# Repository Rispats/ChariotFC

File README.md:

# ChariotFC

> Custom Flight Controller + PDB for General Free Style and Auotpilot applications

## Specs
- **FMU:** AT32F435RMT7 (288Mhz, Hardware FPU)
- **Power Distrubution Board:** 2S-6S LiPo 
- **From Factor:** 30.5mm X 30.5mm Dual stack (FC + PDB)
- **Target Firmware:** PX4, Betaflight

STATUS: PCB Design in progress

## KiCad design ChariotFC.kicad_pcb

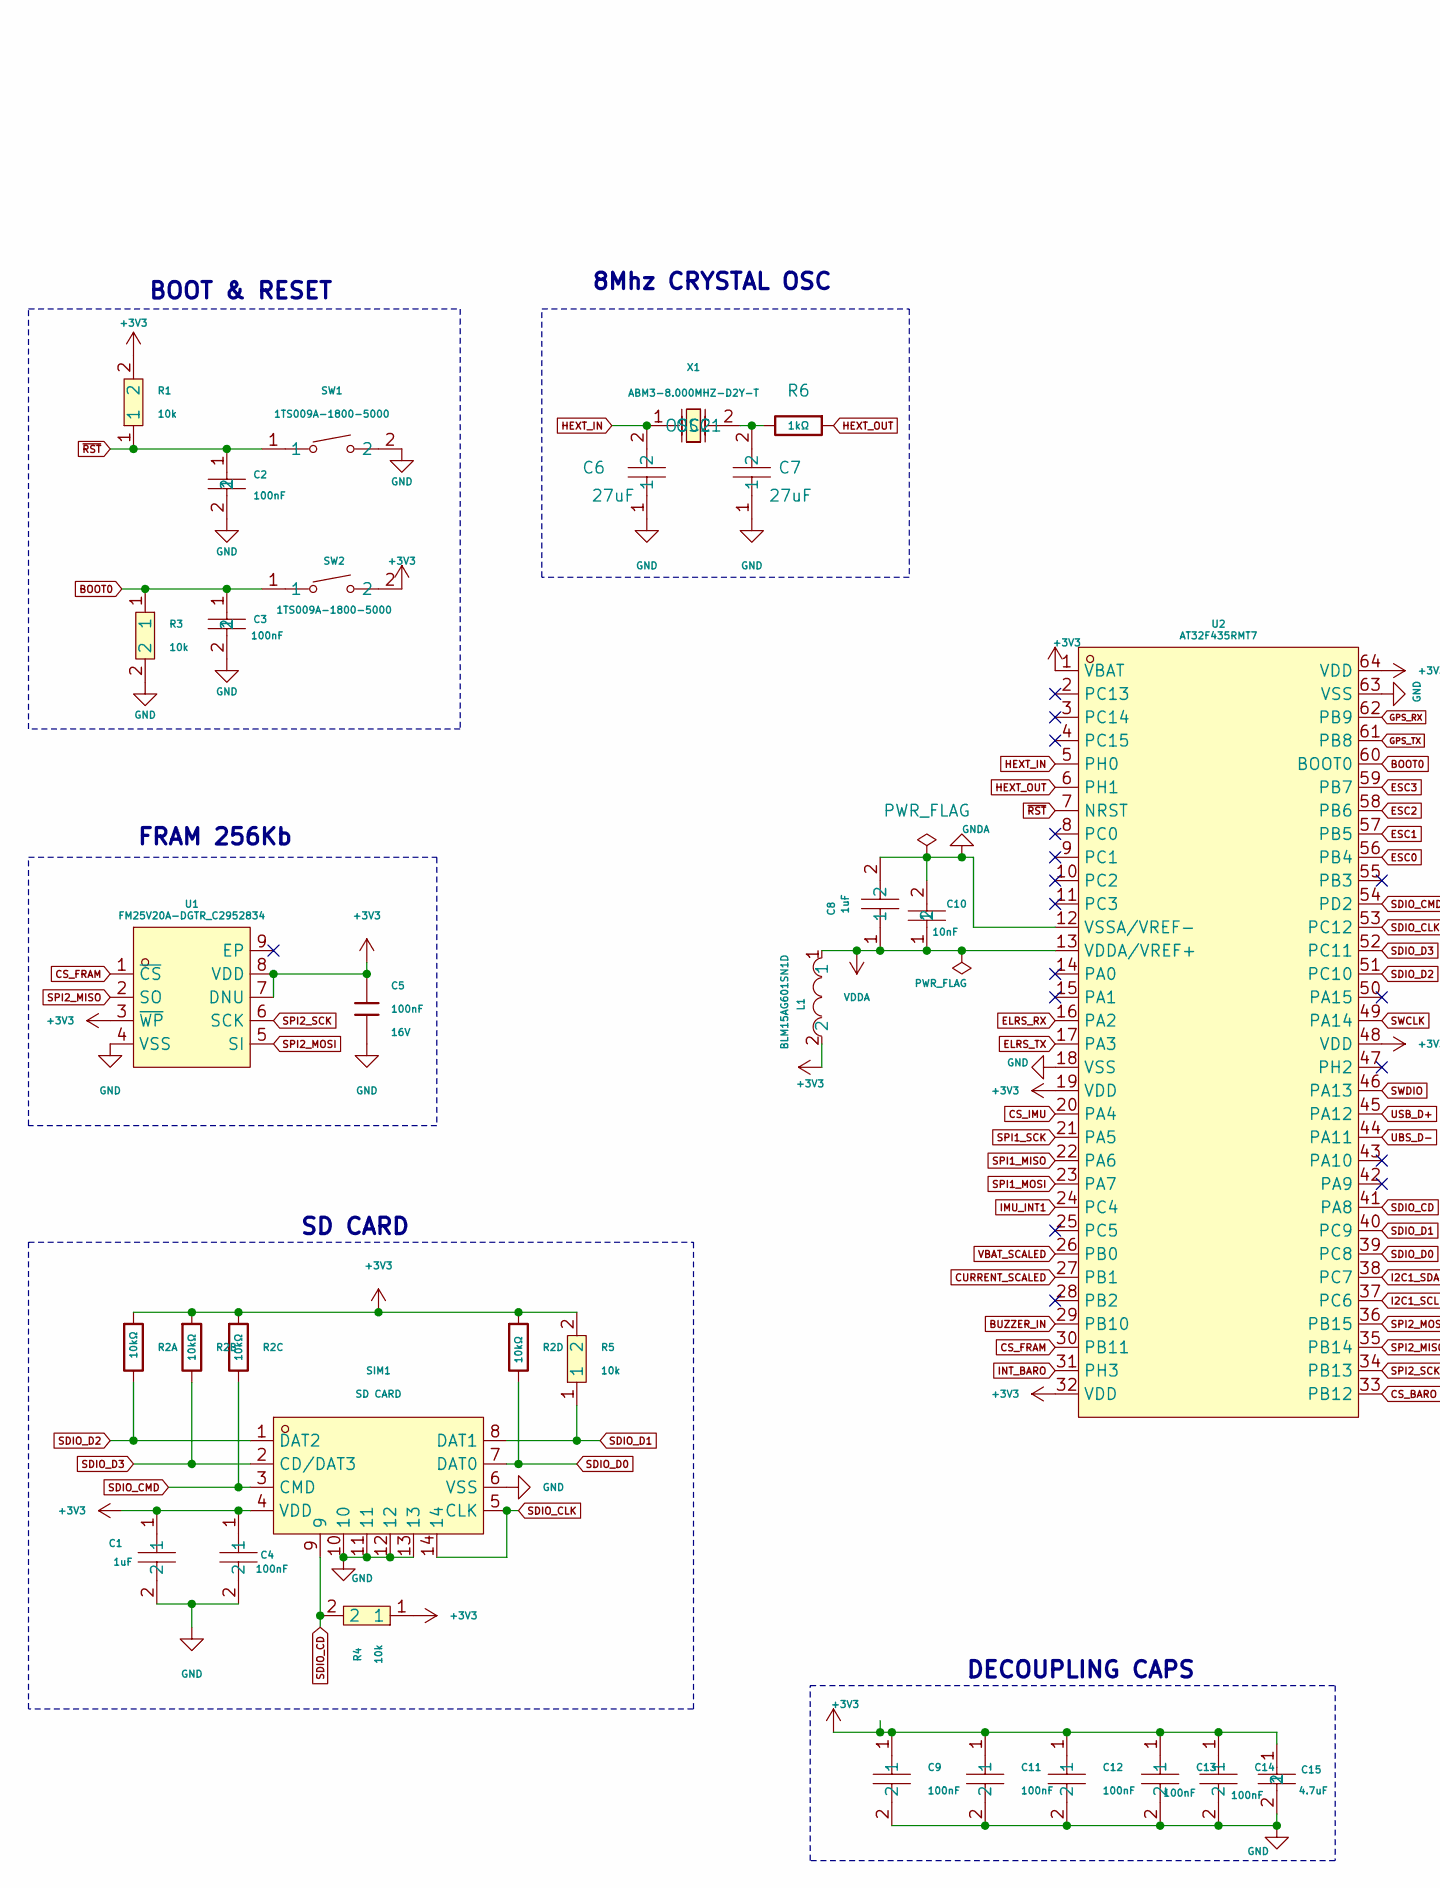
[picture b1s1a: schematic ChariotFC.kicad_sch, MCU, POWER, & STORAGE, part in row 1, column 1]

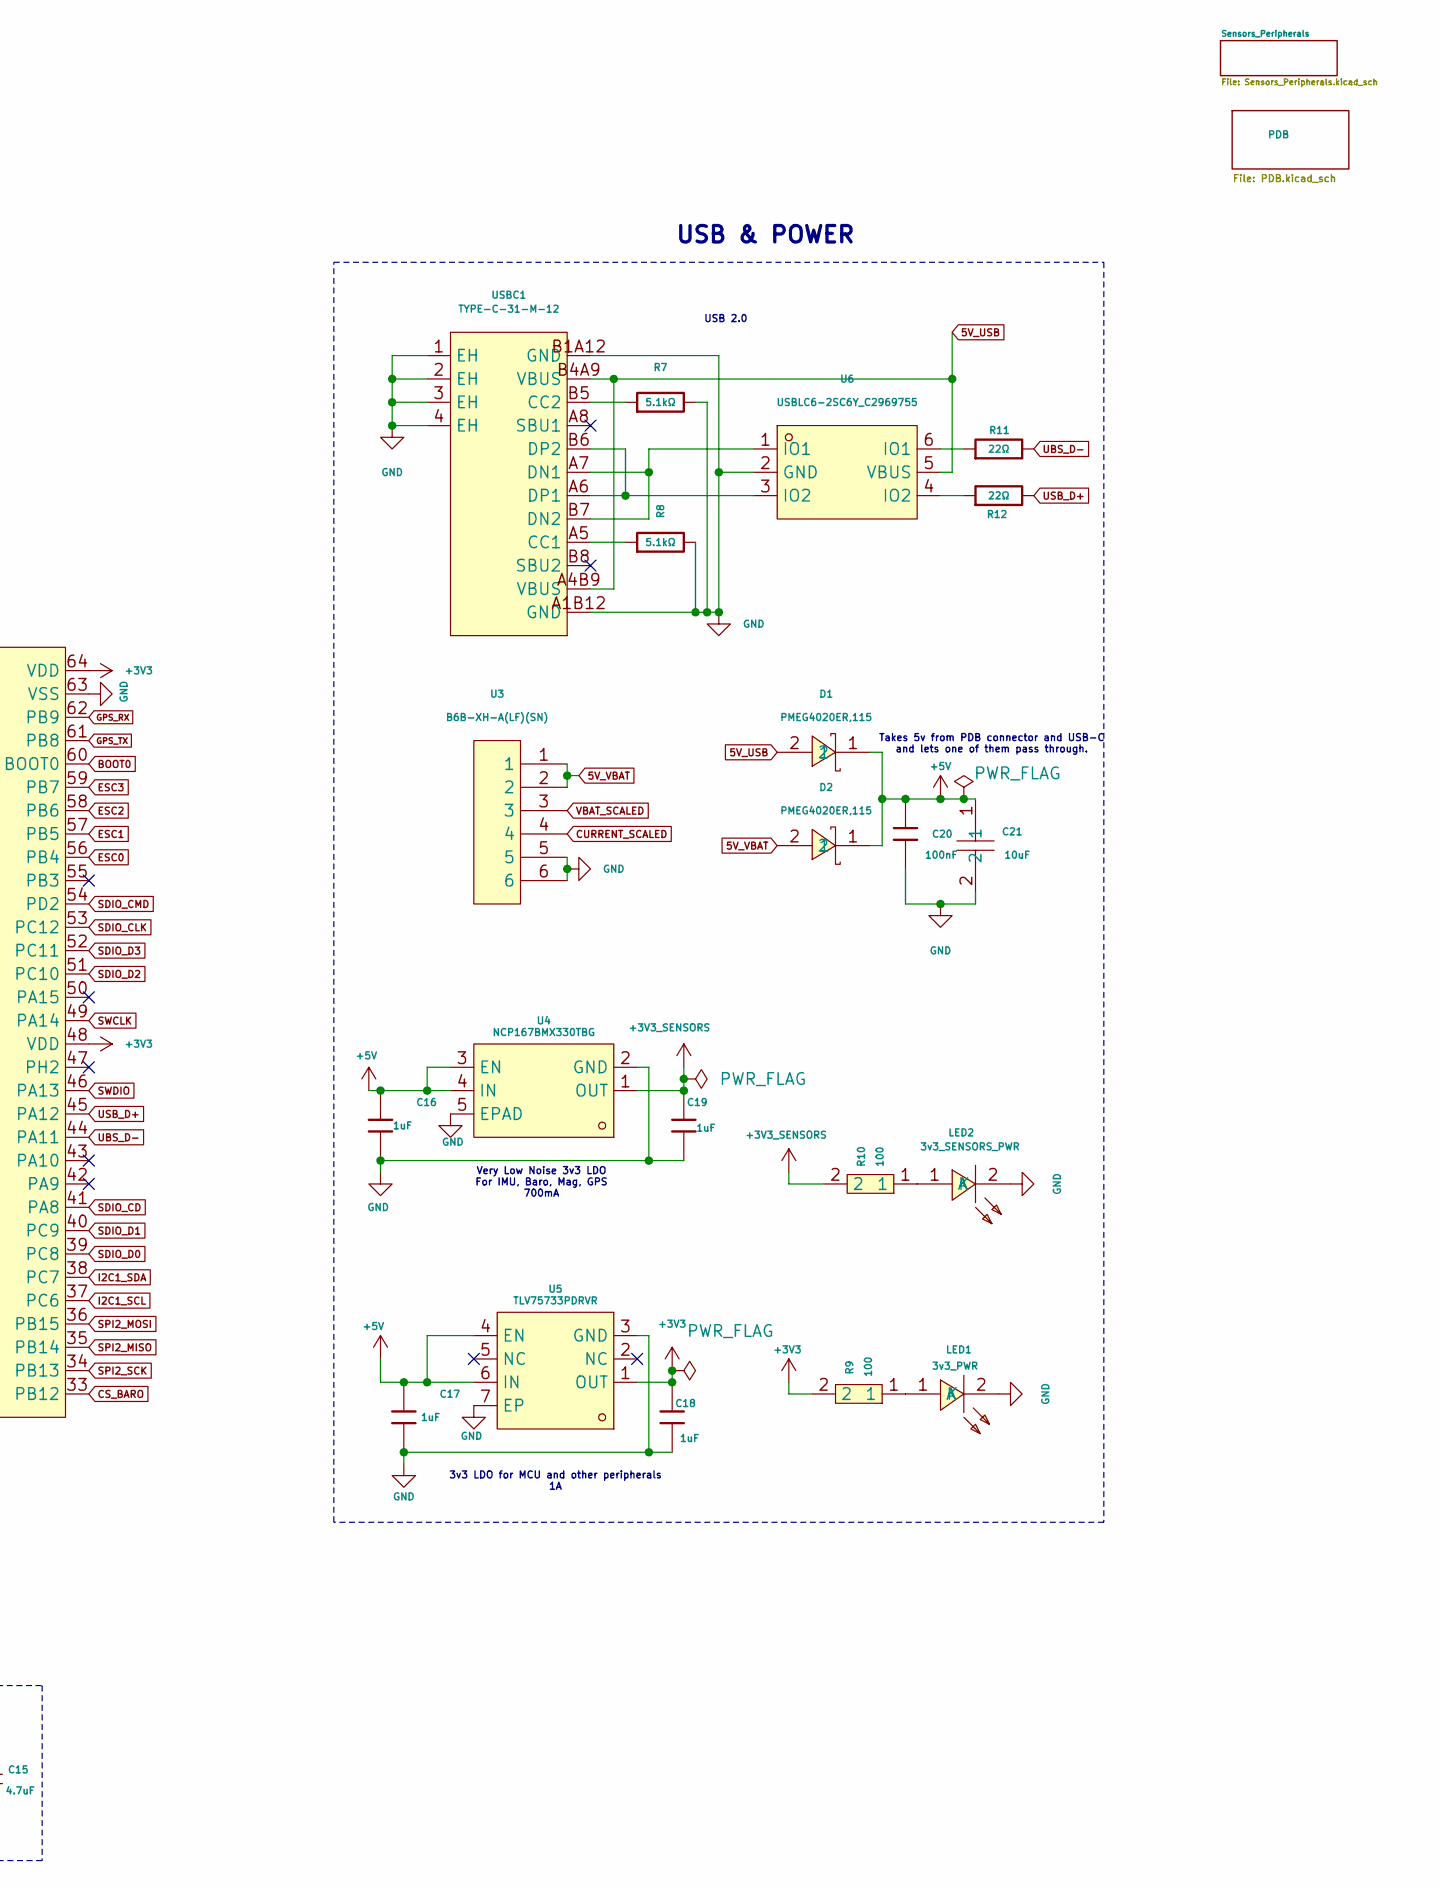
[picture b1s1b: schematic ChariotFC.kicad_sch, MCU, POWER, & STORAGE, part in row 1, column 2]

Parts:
C1: 1uF; C0402; LCSC Part C52923
C2, C3: 100nF; C0402; LCSC Part C77019
C4, C9, C11, C12, C13, C14: 100nF; C0402; LCSC Part C1525
C5, C20: 100nF; C0402; Voltage Rated 16V; Tolerance ±10%; Part CL05B104KO5NNNC; LCSC C1525
C6, C7: 27uF; C0402; LCSC Part C445761
C8: 1uF; C0402; LCSC Part C15684
C10: 10nF; C0402; LCSC Part C77019
C15: 4.7uF; C0805; LCSC Part C1779
C16, C17, C18, C19: 1uF; C0402; Voltage Rated 25V; Tolerance ±10%; Part CL05A105KA5NQNC; LCSC C52923
C21: 10uF; C1206; LCSC Part C6119987
D1, D2: PMEG4020ER,115; SOD-123_L2.8-W1.8-LS3.7-RD; LCSC Part C255588
L1: BLM15AG601SN1D; L0402; LCSC Part C76884
LED1: 3v3_PWR; LED0805-R-RD; LCSC Part C2297
LED2: 3v3_SENSORS_PWR; LED0805-R-RD; LCSC Part C2297
R1, R3, R4, R5: 10k; R0402; LCSC Part C60490
R2: 10kΩ; RES-ARRAY-SMD_0402-8P-L2.0-W1.0-BL; Tolerance ±5%; Part 4D02WGJ0103TCE; LCSC C25725
R6: 1kΩ; R0402; Overload Voltage (Max) 50V; Tolerance ±1%; Part 0402WGF1001TCE; LCSC C11702
R7, R8: 5.1kΩ; R0402; Overload Voltage (Max) 50V; Tolerance ±1%; Part 0402WGF5101TCE; LCSC C25905
R9, R10: 100; R0402; LCSC Part C25076
R11, R12: 22Ω; R0402; Overload Voltage (Max) 50V; Tolerance ±1%; Part 0402WGF220JTCE; LCSC C25092
SIM1: SD CARD; SIM-SMD_8P-1040310811; LCSC Part C585350
SW1, SW2: 1TS009A-1800-5000; KEY-SMD_L6.0-W6.0-LS6.6; LCSC Part C319409
U1: FM25V20A-DGTR_C2952834; DFN-8_L6.0-W5.0-P1.27-BL-EP; LCSC Part C2952834
U2: AT32F435RMT7; LQFP-64_L10.0-W10.0-P0.50-LS12.0-BL; LCSC Part C5178940
U3: B6B-XH-A(LF)(SN); CONN-TH_6P-P2.50_B6B-XH-A-LF-SN; LCSC Part C144397
U4: NCP167BMX330TBG; XDFN-4_L1.0-W1.0-P0.65-BL-EP; LCSC Part C892227
U5: TLV75733PDRVR; TDFN-6_L2.0-W2.0-P0.65-TL-EP; LCSC Part C2868428
U6: USBLC6-2SC6Y_C2969755; SOT-23-6_L2.9-W1.7-P0.95-LS2.8-BL; LCSC Part C2969755
USBC1: TYPE-C-31-M-12; USB-C_SMD-TYPE-C-31-M-12_1; LCSC Part C165948
X1: ABM3-8.000MHZ-D2Y-T; OSC-SMD_L5.0-W3.2; LCSC Part C144380

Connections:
5V_USB: D1.2, U6.5 (VBUS), USBC1.A4B9 (VBUS), USBC1.B4A9 (VBUS)
5V_VBAT: D2.2, U3.1, U3.2; also elsewhere on the board
+3V3: C1.1, C4.1, C5.1, C9.1, C11.1, C12.1, C13.1, C14.1, C15.1, C18.1, L1.2, R1.2, R2.1, R2.2, R2.3, R2.4, R4.1, R5.2, R9.2, SIM1.4 (VDD), SW2.2, U1.3 (~WP), U1.7 (DNU), U1.8 (VDD), U2.1 (VBAT), U2.19 (VDD), U2.32 (VDD), U2.48 (VDD), U2.64 (VDD), U5.1 (OUT); also elsewhere on the board
+3V3_SENSORS: C19.1, R10.2, U4.1 (OUT); also elsewhere on the board
+5V: C16.1, C17.1, C20.2, C21.1, D1.1, D2.1, U4.3 (EN), U4.4 (IN), U5.4 (EN), U5.6 (IN); also elsewhere on the board
BOOT0: C3.1, R3.1, SW2.1, U2.60 (BOOT0)
BUZZER_IN: U2.29 (PB10); also elsewhere on the board
CS_BARO: U2.33 (PB12); also elsewhere on the board
CS_FRAM: U1.1 (~CS), U2.30 (PB11)
CS_IMU: U2.20 (PA4); also elsewhere on the board
CURRENT_SCALED: U2.27 (PB1), U3.4; also elsewhere on the board
ELRS_RX: U2.16 (PA2); also elsewhere on the board
ELRS_TX: U2.17 (PA3); also elsewhere on the board
ESC0: U2.56 (PB4); also elsewhere on the board
ESC1: U2.57 (PB5); also elsewhere on the board
ESC2: U2.58 (PB6); also elsewhere on the board
ESC3: U2.59 (PB7); also elsewhere on the board
GND: C1.2, C2.2, C3.2, C4.2, C5.2, C6.1, C7.1, C9.2, C11.2, C12.2, C13.2, C14.2, C15.2, C16.2, C17.2, C18.2, C19.2, C20.1, C21.2, LED1.2 (K), LED2.2 (K), R3.2, R7.2, R8.2, SIM1.6 (VSS), SIM1.10, SIM1.11, SIM1.12, SIM1.13, SW1.2, U1.4 (VSS), U2.18 (VSS), U2.63 (VSS), U3.5, U3.6, U4.2 (GND), U4.5 (EPAD), U5.3 (GND), U5.7 (EP), U6.2 (GND), USBC1.1 (EH), USBC1.2 (EH), USBC1.3 (EH), USBC1.4 (EH), USBC1.A1B12 (GND), USBC1.B1A12 (GND); also elsewhere on the board
GNDA: C8.2, C10.2, U2.12 (VSSA/VREF-)
GPS_RX: U2.62 (PB9); also elsewhere on the board
GPS_TX: U2.61 (PB8); also elsewhere on the board
HEXT_IN: C6.2, U2.5 (PH0), X1.1 (OSC1); also elsewhere on the board
HEXT_OUT: R6.1, U2.6 (PH1)
I2C1_SCL: U2.37 (PC6); also elsewhere on the board
I2C1_SDA: U2.38 (PC7); also elsewhere on the board
IMU_INT1: U2.24 (PC4); also elsewhere on the board
INT_BARO: U2.31 (PH3); also elsewhere on the board
unnamed: LED1.1 (A), R9.1
unnamed: LED2.1 (A), R10.1
unnamed: R11.1, U6.6 (IO1)
unnamed: R12.1, U6.4 (IO2)
unnamed: R8.1, USBC1.A5 (CC1)
unnamed: R7.1, USBC1.B5 (CC2)
unnamed: U6.1 (IO1), USBC1.A7 (DN1), USBC1.B7 (DN2)
unnamed: U6.3 (IO2), USBC1.A6 (DP1), USBC1.B6 (DP2)
unnamed 56: C7.2, R6.2, X1.2 (OSC2); also elsewhere on the board
SDIO_CD: R4.2, SIM1.9, U2.41 (PA8)
SDIO_CLK: SIM1.5 (CLK), SIM1.14, U2.53 (PC12)
SDIO_CMD: R2.6, SIM1.3 (CMD), U2.54 (PD2)
SDIO_D0: R2.5, SIM1.7 (DAT0), U2.39 (PC8)
SDIO_D1: R5.1, SIM1.8 (DAT1), U2.40 (PC9)
SDIO_D2: R2.8, SIM1.1 (DAT2), U2.51 (PC10)
SDIO_D3: R2.7, SIM1.2 (CD/DAT3), U2.52 (PC11)
SPI1_MISO: U2.22 (PA6); also elsewhere on the board
SPI1_MOSI: U2.23 (PA7); also elsewhere on the board
SPI1_SCK: U2.21 (PA5); also elsewhere on the board
SPI2_MISO: U1.2 (SO), U2.35 (PB14); also elsewhere on the board
SPI2_MOSI: U1.5 (SI), U2.36 (PB15); also elsewhere on the board
SPI2_SCK: U1.6 (SCK), U2.34 (PB13); also elsewhere on the board
SWCLK: U2.49 (PA14); also elsewhere on the board
SWDIO: U2.46 (PA13); also elsewhere on the board
UBS_D-: R11.2, U2.44 (PA11)
USB_D+: R12.2, U2.45 (PA12)
VBAT_SCALED: U2.26 (PB0), U3.3; also elsewhere on the board
VDDA: C8.1, C10.1, L1.1, U2.13 (VDDA/VREF+)
~RST: C2.1, R1.1, SW1.1, U2.7 (NRST)

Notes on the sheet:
3v3 LDO for MCU and other peripherals 1A
USB & POWER
USB 2.0
Takes 5v from PDB connector and USB-C and lets one of them pass through.
SD CARD
DECOUPLING CAPS
BOOT & RESET
FRAM 256Kb
8Mhz CRYSTAL OSC
Very Low Noise 3v3 LDO For IMU, Baro, Mag, GPS 700mA

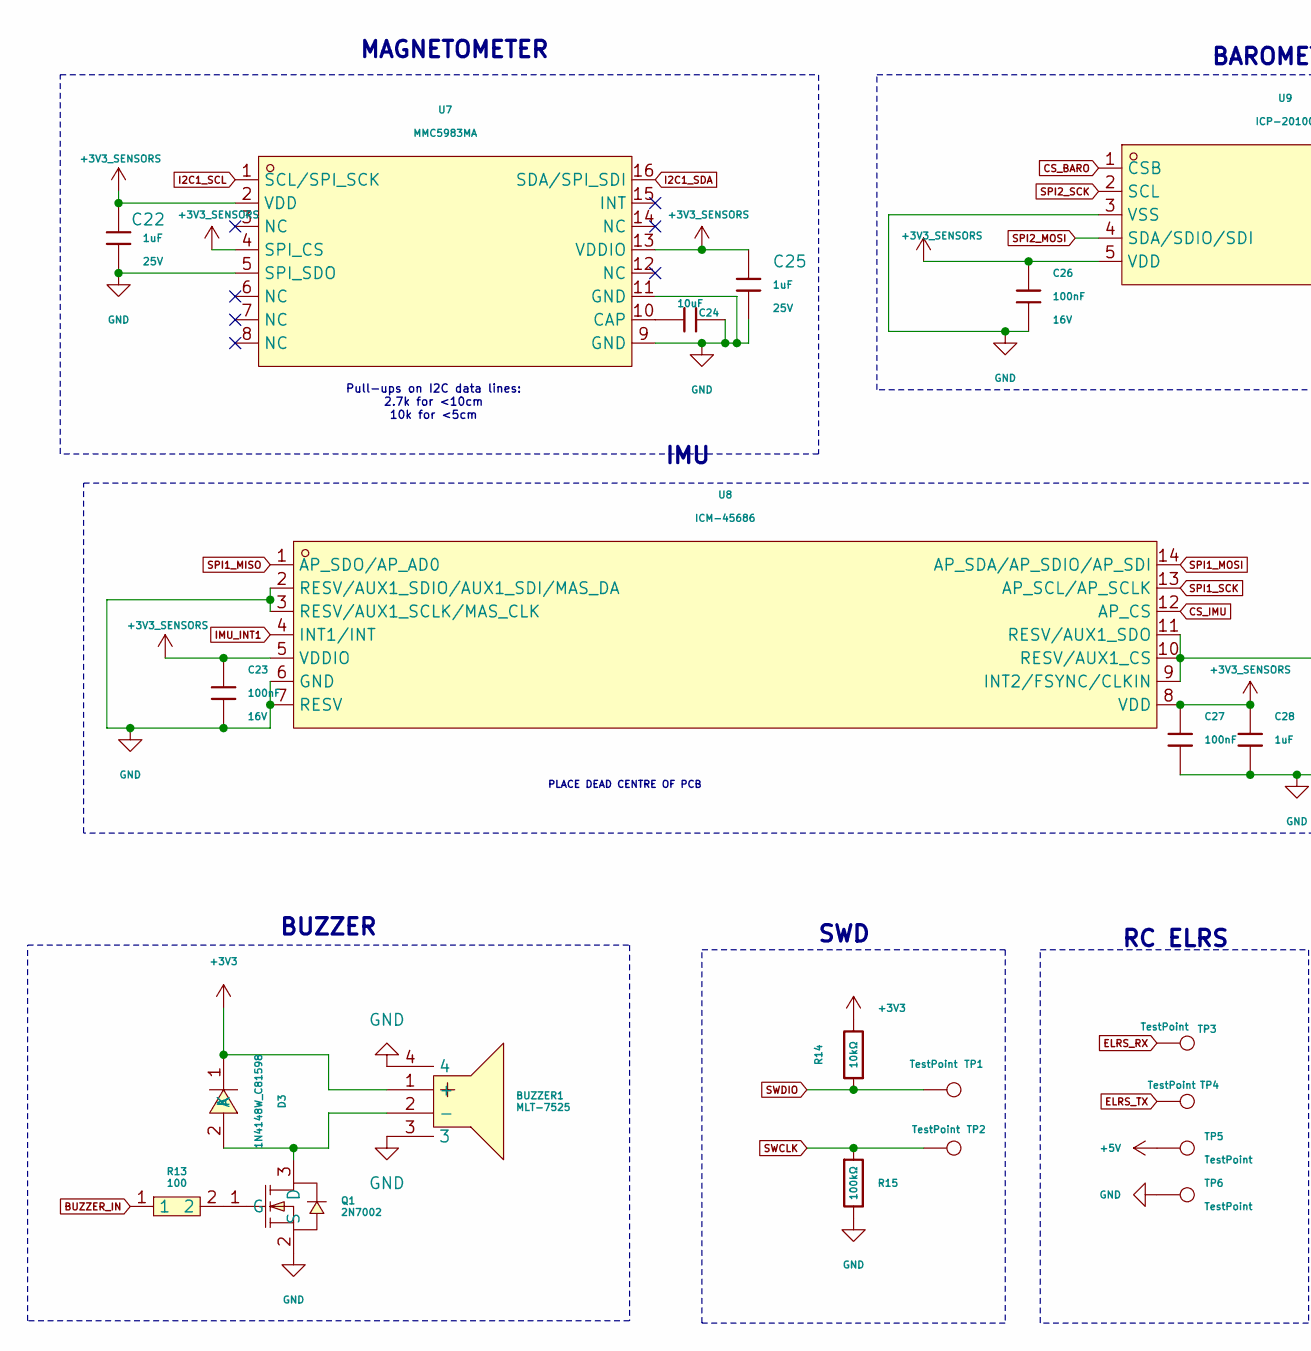
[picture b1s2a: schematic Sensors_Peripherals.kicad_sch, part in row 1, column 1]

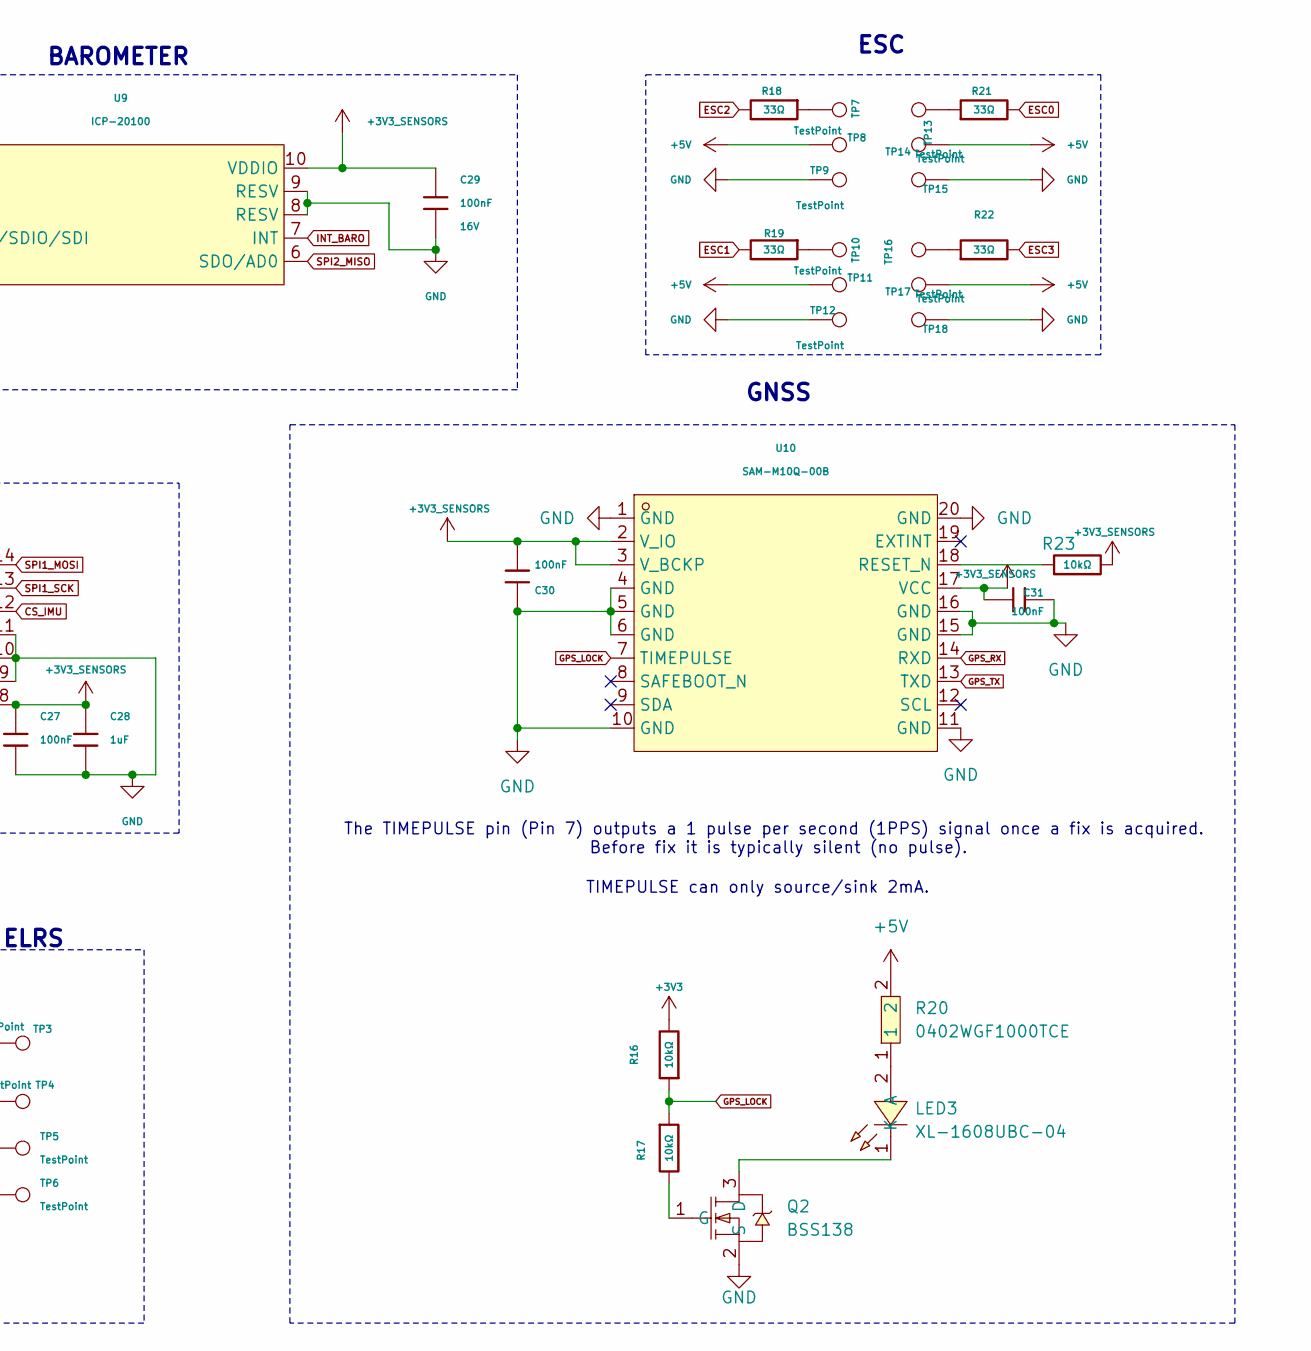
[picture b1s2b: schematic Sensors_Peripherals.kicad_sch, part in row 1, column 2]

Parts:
BUZZER1: MLT-7525; BUZ-SMD_4P-L7.5-W7.5-P7.59-TL; LCSC Part C95299
C22, C25, C28: 1uF; C0402; Voltage Rated 25V; Tolerance ±10%; Part CL05A105KA5NQNC; LCSC C52923
C23, C26, C27, C29, C30, C31: 100nF; C0402; Voltage Rated 16V; Tolerance ±10%; Part CL05B104KO5NNNC; LCSC C1525
C24: 10uF; C0603; Voltage Rated 10V; Tolerance ±10%; Part CL10A106KP8NNNC; LCSC C19702
D3: 1N4148W_C81598; SOD-123F_L2.7-W1.6-LS3.8-RD; LCSC Part C81598
LED3: XL-1608UBC-04; LED0603-RD_BLUE; MPN XL-1608UBC-04; LCSC Part C965807
Q1: 2N7002; SOT-23-3_L2.9-W1.3-P1.90-LS2.4-BR; LCSC Part C8545
Q2: BSS138; SOT-23-3_L2.9-W1.6-P1.90-LS2.8-BR; MPN BSS138; LCSC Part C52895
R13: 100; R0402; LCSC Part C25076
R14, R16, R17: 10kΩ; R0402; Overload Voltage (Max) 50V; Tolerance ±1%; Part 0402WGF1002TCE; LCSC C25744
R15: 100kΩ; R0402; Overload Voltage (Max) 50V; Tolerance ±1%; Part 0402WGF1003TCE; LCSC C25741
R18, R19: 33Ω; R0402; Overload Voltage (Max) 50V; Tolerance ±1%; Part 0402WGF330JTCE; LCSC C25105
R20: 0402WGF1000TCE; R0402; MPN 0402WGF1000TCE; LCSC Part C25076
R21, R22: 33Ω; C0402; Overload Voltage (Max) 50V; Tolerance ±1%; Part 0402WGF330JTCE; LCSC C25105
R23: 10kΩ; C0402; Overload Voltage (Max) 50V; Tolerance ±1%; Part 0402WGF1002TCE; LCSC C25744
TP1, TP2: TestPoint; TestPoint_THTPad_D2.0mm_Drill1.0mm
TP3, TP4, TP5, TP6, TP7, TP8, TP9, TP10, TP11, TP12, TP13, TP14, TP15, TP16, TP17, TP18: TestPoint; TestPoint_Pad_4.0x4.0mm
U7: MMC5983MA; LGA-16_L3.0-W3.0-P0.50-BL_SQ; LCSC Part C404329
U8: ICM-45686; LGA-14_L3.0-W2.5-P0.50-TL; LCSC Part C22459454
U9: ICP-20100; LGA-10_L2.0-W2.0-P0.50-TL_ICP-20100; LCSC Part C5343527
U10: SAM-M10Q-00B; LCC-20_L15.5-W15.5-P1.90_SAM-M10Q-00B; LCSC Part C5443880

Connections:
+3V3: BUZZER1.1 (+), D3.1 (K), R14.2, R16.2; also elsewhere on the board
+3V3_SENSORS: C22.1, C23.1, C25.1, C26.2, C27.1, C28.1, C29.1, C30.1, C31.1, R23.2, U7.2 (VDD), U7.4 (SPI_CS), U7.13 (VDDIO), U8.5 (VDDIO), U8.8 (VDD), U9.5 (VDD), U9.10 (VDDIO), U10.2 (V_IO), U10.3 (V_BCKP), U10.17 (VCC); also elsewhere on the board
+5V: R20.2, TP5.1 (1_1), TP8.1 (1_1), TP11.1 (1_1), TP14.1 (1_1), TP17.1 (1_1); also elsewhere on the board
BUZZER_IN: R13.1; also elsewhere on the board
CS_BARO: U9.1 (CSB); also elsewhere on the board
CS_IMU: U8.12 (AP_CS); also elsewhere on the board
ELRS_RX: TP3.1 (1_1); also elsewhere on the board
ELRS_TX: TP4.1 (1_1); also elsewhere on the board
ESC0: R21.2; also elsewhere on the board
ESC1: R19.2; also elsewhere on the board
ESC2: R18.2; also elsewhere on the board
ESC3: R22.2; also elsewhere on the board
GND: BUZZER1.3, BUZZER1.4, C22.2, C23.2, C24.2, C25.2, C26.1, C27.2, C28.2, C29.2, C30.2, C31.2, Q1.2 (S), Q2.2 (S), R15.2, TP6.1 (1_1), TP9.1 (1_1), TP12.1 (1_1), TP15.1 (1_1), TP18.1 (1_1), U7.5 (SPI_SDO), U7.9 (GND), U7.11 (GND), U8.2 (RESV/AUX1_SDIO/AUX1_SDI/MAS_DA), U8.3 (RESV/AUX1_SCLK/MAS_CLK), U8.6 (GND), U8.7 (RESV), U8.9 (INT2/FSYNC/CLKIN), U8.10 (RESV/AUX1_CS), U8.11 (RESV/AUX1_SDO), U9.3 (VSS), U9.8 (RESV), U9.9 (RESV), U10.1 (GND), U10.4 (GND), U10.5 (GND), U10.6 (GND), U10.10 (GND), U10.11 (GND), U10.15 (GND), U10.16 (GND), U10.20 (GND); also elsewhere on the board
GPS_LOCK: R16.1, R17.1, U10.7 (TIMEPULSE)
GPS_RX: U10.14 (RXD); also elsewhere on the board
GPS_TX: U10.13 (TXD); also elsewhere on the board
I2C1_SCL: U7.1 (SCL/SPI_SCK); also elsewhere on the board
I2C1_SDA: U7.16 (SDA/SPI_SDI); also elsewhere on the board
IMU_INT1: U8.4 (INT1/INT); also elsewhere on the board
INT_BARO: U9.7 (INT); also elsewhere on the board
unnamed: BUZZER1.2 (-), D3.2 (A), Q1.3 (D)
unnamed: LED3.2 (A), R20.1
unnamed: LED3.1 (K), Q2.3 (D)
unnamed: Q1.1 (G), R13.2
unnamed: Q2.1 (G), R17.2
unnamed: R18.1, TP7.1 (1_1)
unnamed: R19.1, TP10.1 (1_1)
unnamed: R21.1, TP13.1 (1_1)
unnamed: R22.1, TP16.1 (1_1)
unnamed: C24.1, U7.10 (CAP)
unnamed: R23.1, U10.18 (RESET_N)
SPI1_MISO: U8.1 (AP_SDO/AP_AD0); also elsewhere on the board
SPI1_MOSI: U8.14 (AP_SDA/AP_SDIO/AP_SDI); also elsewhere on the board
SPI1_SCK: U8.13 (AP_SCL/AP_SCLK); also elsewhere on the board
SPI2_MISO: U9.6 (SDO/AD0); also elsewhere on the board
SPI2_MOSI: U9.4 (SDA/SDIO/SDI); also elsewhere on the board
SPI2_SCK: U9.2 (SCL); also elsewhere on the board
SWCLK: R15.1, TP2.1 (1_1); also elsewhere on the board
SWDIO: R14.1, TP1.1 (1_1); also elsewhere on the board

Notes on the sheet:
BAROMETER
ESC
SWD
The TIMEPULSE pin (Pin 7) outputs a 1 pulse per second (1PPS) signal once a fix is acquired. Before fix it is typically silent (no pulse).
IMU
PLACE DEAD CENTRE OF PCB
TIMEPULSE can only source/sink 2mA.
MAGNETOMETER
RC ELRS
GNSS
BUZZER
Pull-ups on I2C data lines: 2.7k for <10cm 10k for <5cm

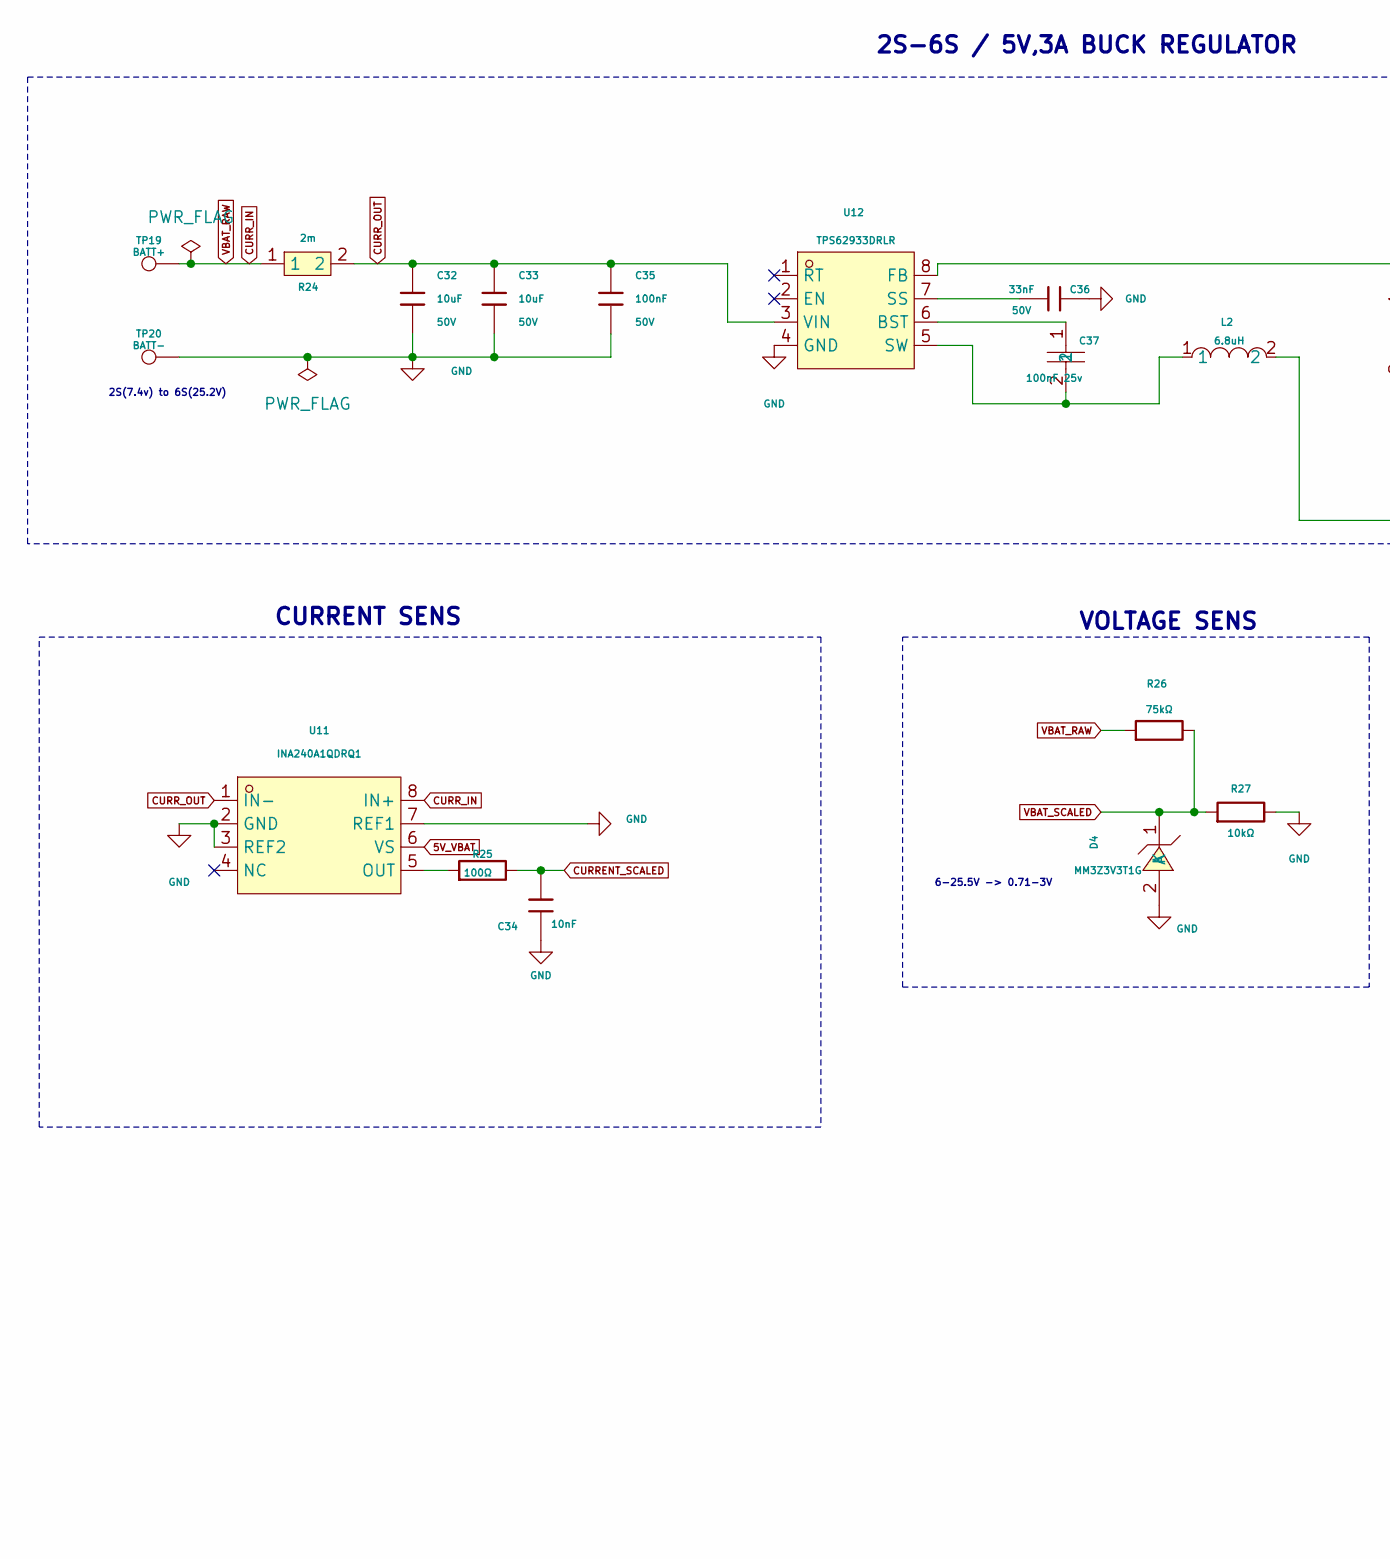
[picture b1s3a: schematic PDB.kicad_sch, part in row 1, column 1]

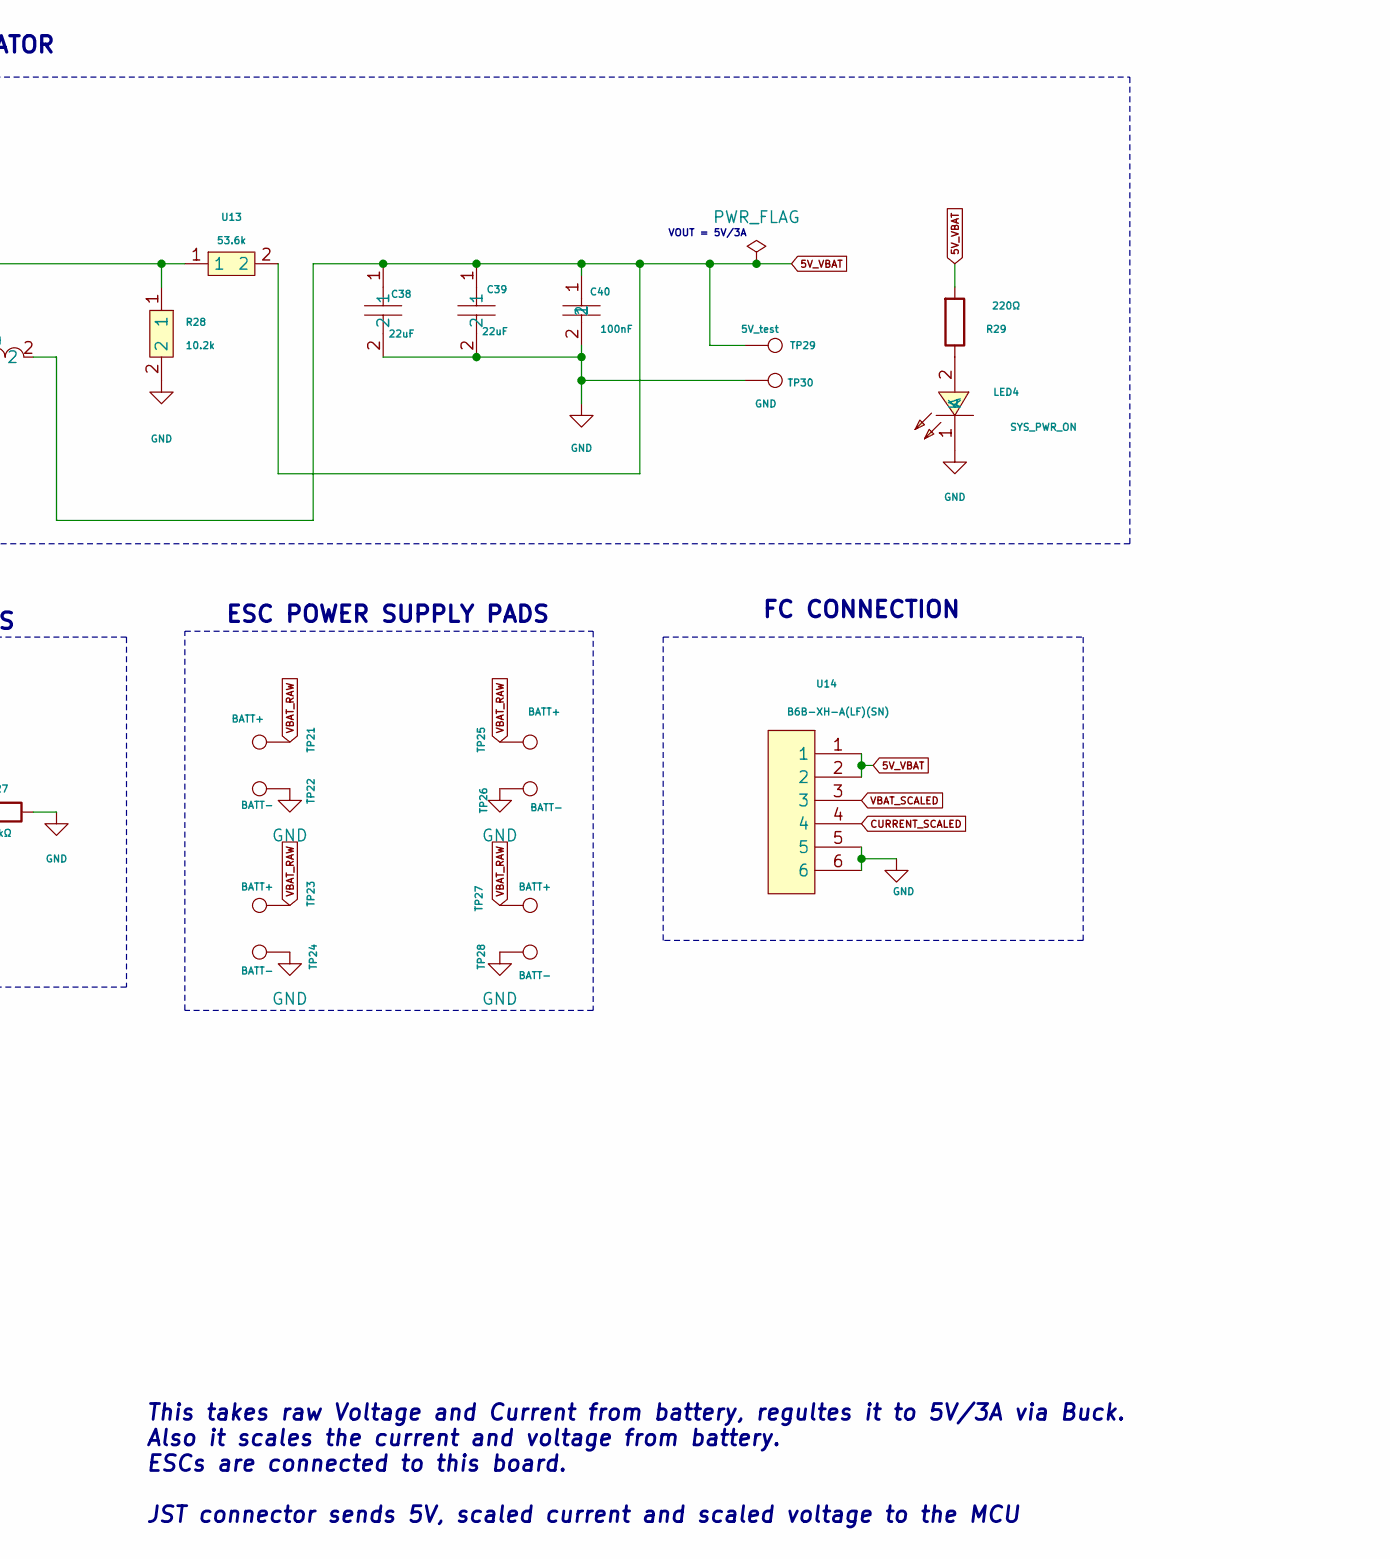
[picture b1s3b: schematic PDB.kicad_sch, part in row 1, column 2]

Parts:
C32, C33: 10uF; C0805; Voltage Rated 50V; Tolerance ±10%; Part GRM21BR61H106KE43L; LCSC C440198
C34: 10nF; C0402; Voltage Rated 50V; Tolerance ±10%; Part CL05B103KB5NNNC; LCSC C15195
C35: 100nF; C0402; Voltage Rated 50V; Tolerance ±10%; Part CL05B104KB54PNC; LCSC C307331
C36: 33nF; C0603; Voltage Rated 50V; Tolerance ±10%; Part CL10B333KB8NNNC; LCSC C21117
C37: 100nF 25v; C0402; LCSC Part C100072
C38, C39: 22uF; C1206; LCSC Part C91604
C40: 100nF; C0402; LCSC Part C100072
D4: MM3Z3V3T1G; SOD-323_L1.8-W1.3-LS2.5-RD; LCSC Part C75073
L2: 6.8uH; IND-SMD_L7.1-W6.6; LCSC Part C5349706
LED4: SYS_PWR_ON; LED0603-RD; LCSC Part C2286
R24: 2m; RES-SMD_L6.4-W3.2-1; LCSC Part C2994640
R25: 100Ω; R0402; Overload Voltage (Max) 50V; Tolerance ±1%; Part 0402WGF1000TCE; LCSC C25076
R26: 75kΩ; R0402; Overload Voltage (Max) 50V; Tolerance ±1%; Part 0402WGF7502TCE; LCSC C25798
R27: 10kΩ; R0402; Overload Voltage (Max) 50V; Tolerance ±1%; Part 0402WGF1002TCE; LCSC C25744
R28: 10.2k; R0805; LCSC Part C2933282
R29: 220Ω; R0603; Overload Voltage (Max) 75V; Tolerance ±1%; Part 0603WAF2200T5E; LCSC C22962
TP19, TP21, TP23, TP25, TP27: BATT+; TestPoint_Pad_4.0x4.0mm
TP20, TP22, TP24, TP26, TP28: BATT-; TestPoint_Pad_4.0x4.0mm
TP29: 5V_test; TestPoint_Pad_D2.0mm
TP30: GND; TestPoint_Pad_4.0x4.0mm
U11: INA240A1QDRQ1; SOIC-8_L4.9-W3.9-P1.27-LS6.0-BL-2; LCSC Part C2057377
U12: TPS62933DRLR; SOT-583-8_L2.1-W1.2-P0.50-LS1.6-BR; LCSC Part C3200405
U13: 53.6k; R0603; LCSC Part C2930115
U14: B6B-XH-A(LF)(SN); CONN-TH_6P-P2.50_B6B-XH-A-LF-SN; LCSC Part C144397

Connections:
5V_VBAT: C38.1, C39.1, C40.1, L2.2, R29.1, TP29.1 (1_1), U11.6 (VS), U13.2, U14.1, U14.2; also elsewhere on the board
CURRENT_SCALED: C34.2, R25.2, U14.4; also elsewhere on the board
CURR_IN: R24.1, R26.1, TP19.1 (1_1), TP21.1 (1_1), TP23.1 (1_1), TP25.1 (1_1), TP27.1 (1_1), U11.8 (IN+)
CURR_OUT: C32.1, C33.1, C35.1, R24.2, U11.1 (IN-), U12.3 (VIN)
GND: C32.2, C33.2, C34.1, C35.2, C36.2, C38.2, C39.2, C40.2, D4.2 (A), LED4.1 (K), R27.2, R28.2, TP20.1 (1_1), TP22.1 (1_1), TP24.1 (1_1), TP26.1 (1_1), TP28.1 (1_1), TP30.1 (1_1), U11.2 (GND), U11.3 (REF2), U11.7 (REF1), U12.4 (GND), U14.5, U14.6; also elsewhere on the board
unnamed: LED4.2 (A), R29.2
unnamed: R25.1, U11.5 (OUT)
unnamed: C37.1, U12.6 (BST)
unnamed: R28.1, U12.8 (FB), U13.1
unnamed: C36.1, U12.7 (SS)
unnamed: C37.2, L2.1, U12.5 (SW)
VBAT_SCALED: D4.1 (K), R26.2, R27.1, U14.3; also elsewhere on the board

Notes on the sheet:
FC CONNECTION
VOLTAGE SENS
This takes raw Voltage and Current from battery, regultes it to 5V/3A via Buck. Also it scales the current and voltage from battery. ESCs are connected to this board. JST connector sends 5V, scaled current and scaled voltage to the MCU
ESC POWER SUPPLY PADS
2S-6S / 5V,3A BUCK REGULATOR
2S(7.4v) to 6S(25.2V)
VOUT = 5V/3A
6-25.5V -> 0.71-3V
CURRENT SENS

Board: 2 copper layers, 134 parts (0 on the bottom side), 76 nets, no tracks yet.

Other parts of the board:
C41, C42: 27uF; C0402
LED5: SYS_PWR_ON; LED0603-RD

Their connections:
GND: C41.1, C42.1, LED5.1 (K); also elsewhere on the board
HEXT_IN: C41.2; also elsewhere on the board
unnamed 56: C42.2; also elsewhere on the board

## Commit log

2026-04-09 init: ChariotFC Kicacd project
2026-04-09 Update README with project status
2026-04-11 corrected current sens and voltage sens to filter scaled current reading using RC filter and clamp voltage to 3.3 in case of over voltage respectiveley
2026-04-11 GPS connections made
2026-04-11 Cleaned up circuit
2026-04-12 Added PWR flags, Changed MCU pins electrical characteristics to bidirectional, rectified some ERC errors
2026-04-20 Put the orrect load capacitances fo the External Osc
2026-05-09 Assigned proper footprints, Re-annotated, Connection modification for efficient PCB layout, First PCB update
2026-05-09 Update power distribution board specs and status
2026-05-12 Joind PDB Batt+ and Batt- pads to LiPo battery input net
2026-05-12 Status changes in readme
